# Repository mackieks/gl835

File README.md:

very basic GL835 reference design in KiCAD 8.99

## License
Solderpad Hardware License v2.1

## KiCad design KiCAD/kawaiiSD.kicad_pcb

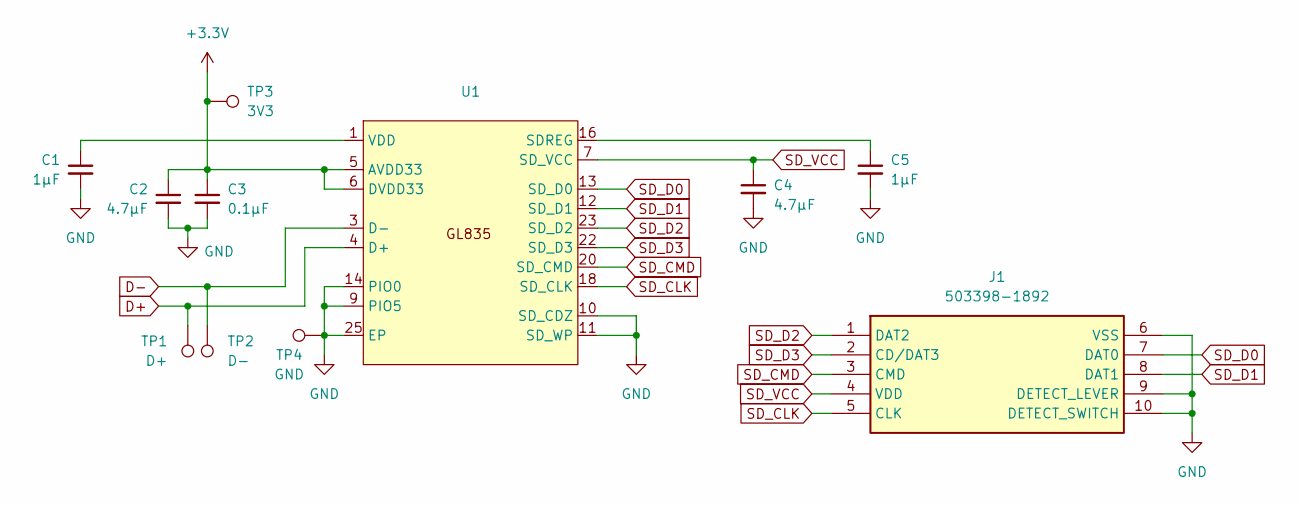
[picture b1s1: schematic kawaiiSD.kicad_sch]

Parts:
C1, C5: 1μF; C_0402_1005Metric
C2, C4: 4.7μF; C_0603_1608Metric
C3: 0.1μF; C_0402_1005Metric
J1: 503398-1892; Mouser Part Number 538-503398-1892
TP1: D+; TestPoint_Pad_D1.5mm
TP2: D-; TestPoint_Pad_D1.5mm
TP3: 3V3; TestPoint_Pad_D1.5mm
TP4: GND; TestPoint_Pad_D1.5mm
U1: HVQFN-24-1EP_4x4mm_P0.5mm_EP2.5x2.5mm

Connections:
+3.3V: C2.1, C3.1, TP3.1, U1.5 (AVDD33), U1.6 (DVDD33)
D+: TP1.1, U1.4 (D+)
D-: TP2.1, U1.3 (D-)
GND: C1.2, C2.2, C3.2, C4.2, C5.2, J1.6 (VSS), J1.9 (DETECT_LEVER), J1.10 (DETECT_SWITCH), J1.11, J1.12, J1.13, J1.14, TP4.1, U1.9 (PIO5), U1.10 (SD_CDZ), U1.11 (SD_WP), U1.14 (PIO0), U1.25 (EP)
unnamed: C5.1, U1.16 (SDREG)
unnamed: C1.1, U1.1 (VDD)
SD_CLK: J1.5 (CLK), U1.18 (SD_CLK)
SD_CMD: J1.3 (CMD), U1.20 (SD_CMD)
SD_D0: J1.7 (DAT0), U1.13 (SD_D0)
SD_D1: J1.8 (DAT1), U1.12 (SD_D1)
SD_D2: J1.1 (DAT2), U1.23 (SD_D2)
SD_D3: J1.2 (CD/DAT3), U1.22 (SD_D3)
SD_VCC: C4.1, J1.4 (VDD), U1.7 (SD_VCC)

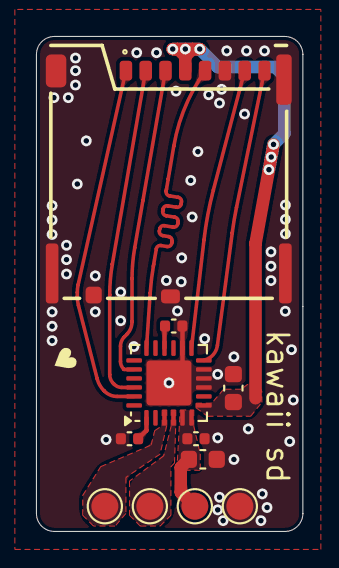
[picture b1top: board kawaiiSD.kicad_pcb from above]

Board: 2 copper layers, 14.8 x 27.5 mm, 11 parts (0 on the bottom side), 13 nets.
